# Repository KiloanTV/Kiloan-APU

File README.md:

<div>
  <h1 align="center">Kiloan APU V1</h1>

  <p align="center">
  <a href="https://hackclub.com/highway">
    </img>
  </a>
  </p>
  <h1></h1>
  <p align="center">
    The mainboard for a custom digital mixing console!
  </p>
</div>

<sub align="center">This work is licensed under the
[MIT License](https://mit-license.org).
</sub>

## Table of Contents

- [About](#about)
- [Pictures](#pictures)
- [Bill of Materials](#bill-of-materials)

# About

I've always wanted my own digital mixing console, but those things are just too expensive for teenagers. That's why I want to build my own! This is the mainboard, to which additional PCB boards will later be attached. They provide inputs/outputs (balanced XLR, of course), are responsible for the controls, and serve as a USB audio interface. This is the first step in this extensive project!

# Pictures

# Bill of Materials

|Reference                                        |Value                        |Description                                                                                                                 |Qty|LCSC           |Price|FIELD7                 |
|-------------------------------------------------|-----------------------------|----------------------------------------------------------------------------------------------------------------------------|---|---------------|-----|-----------------------|
|C1                                               |25V 10u0                     |                                                                                                                            |1  |C391262        |     |                       |
|C2,C5,C13,C20,C28,C30,C31,C32,C33,C35,C36,C37,C38|CAP_100n_50V_X7R_0805        |                                                                                                                            |13 |C3018562       |     |                       |
|C3,C4,C6,C18,C19,C21,C29,C34                     |CAP_10u0_25V_X5R_0805        |                                                                                                                            |8  |C391262        |     |                       |
|C7,C10                                           |25V 10uF                     |25V 10uF X5R ±20% 0805 Multilayer Ceramic Capacitors MLCC - SMD/SMT ROHS                                                    |2  |C391262        |     |                       |
|C8,C11                                           |50V 100nF                    |50V 100nF X7R ±10% 0805 Multilayer Ceramic Capacitors MLCC - SMD/SMT ROHS                                                   |2  |C3018562       |     |                       |
|C9                                               |50V 5.6nF                    |50V 5.6nF X7R ±10% 0805 Multilayer Ceramic Capacitors MLCC - SMD/SMT ROHS                                                   |1  |C113862        |     |                       |
|C12                                              |50V 150pF                    |50V 150pF C0G ±5% 0805 Multilayer Ceramic Capacitors MLCC - SMD/SMT ROHS                                                    |1  |C2168780       |     |                       |
|C14,C15                                          |50V 12pF                     |                                                                                                                            |2  |C2168859       |     |                       |
|C16,C17,C25,C26,C27                              |CAP_100u_20%_25V_ALUM_RADIAL |                                                                                                                            |5  |C108360,C136287|     |                       |
|C22,C23,C24                                      |330u_20%_25V_ALUM_RADIAL     |                                                                                                                            |3  |C47344178      |     |                       |
|FER1,FER2                                        |210mΩ 0805                   |210mΩ ±25% 600Ω@100MHz 0805 Ferrite Beads ROHS                                                                              |2  |C85837         |     |                       |
|IC1,IC5                                          |IC_LM1117MP-5.0              |                                                                                                                            |2  |C131933        |     |                       |
|IC2                                              |IC_NCP1117LPST33             |                                                                                                                            |1  |C146799        |     |                       |
|IC3                                              |IC_ADM811TARTZ               |                                                                                                                            |1  |C462205        |     |                       |
|IC4                                              |IC_TLE2426ID                 |                                                                                                                            |1  |C59459         |     |                       |
|IC6                                              |IC_25AA1024                  |                                                                                                                            |1  |C2653525       |     |                       |
|J1                                               |PowerConAD-Wandler           |Generic connector, single row, 01x04, script generated (kicad-library-utils/schlib/autogen/connector/)                      |1  |C131334        |     |                       |
|J2                                               |AD-Wandler CON               |Generic connector, single row, 01x08, script generated (kicad-library-utils/schlib/autogen/connector/)                      |1  |C157974        |     |                       |
|J3                                               |PowerConDA-Wandler           |Generic connector, single row, 01x04, script generated (kicad-library-utils/schlib/autogen/connector/)                      |1  |C131334        |     |                       |
|J4                                               |DA-Wandler CON               |Generic connector, single row, 01x08, script generated (kicad-library-utils/schlib/autogen/connector/)                      |1  |C157974        |     |                       |
|J5                                               |PowerCON ESP                 |Generic connector, single row, 01x02, script generated (kicad-library-utils/schlib/autogen/connector/)                      |1  |C131337        |     |                       |
|J6                                               |ESP CON                      |Generic connector, single row, 01x08, script generated (kicad-library-utils/schlib/autogen/connector/)                      |1  |C157974        |     |                       |
|J7                                               |PowerConXMOS                 |Generic connector, single row, 01x04, script generated (kicad-library-utils/schlib/autogen/connector/)                      |1  |C131334        |     |                       |
|J8                                               |XMOS CON                     |Generic connector, single row, 01x08, script generated (kicad-library-utils/schlib/autogen/connector/)                      |1  |C157974        |     |                       |
|J9                                               |AUXADC                       |Generic connector, single row, 01x05, script generated (kicad-library-utils/schlib/autogen/connector/)                      |1  |C157993        |     |                       |
|JP1                                              |CON_JUMPER                   |                                                                                                                            |1  |C492401        |     |                       |
|P1                                               |ADAU1452                     |Audio Processing Unit                                                                                                       |1  |C462188        |     |                       |
|Q1                                               |ST STD2805T4                 |PNP 60V 5A 150MHz 15W                                                                                                       |1  |C672201        |     |                       |
|R1,R2                                            |RES_2K00_1%_0.125W_Thick_0805|                                                                                                                            |2  |C114572        |     |                       |
|R3,R4,R7,R8                                      |33R0_5%_4x0603               |                                                                                                                            |4  |C872331        |     |                       |
|R5                                               |1kΩ 0805                     |125mW Thick Film Resistor 150V ±100ppm/℃ ±1% 1kΩ 0805 Chip Resistor - Surface Mount ROHS                                    |1  |C95781         |     |                       |
|R9                                               |RES_1K00_1%_0.125W_Thick_0805|                                                                                                                            |1  |C95781         |     |                       |
|R10                                              |4.32kΩ                       |125mW Thick Film Resistor 150V ±100ppm/℃ ±1% 4.32kΩ 0805 Chip Resistor - Surface Mount ROHS                                 |1  |C483139        |     |                       |
|R11                                              |RES_100K_1%_0.125W_Thick_0805|                                                                                                                            |1  |C96346         |     |                       |
|R12,R15,R16                                      |RES_10K0_1%_0.125W_Thick_0805|                                                                                                                            |3  |C84376         |     |                       |
|R13                                              |RES_33R0_1%_0.125W_Thick_0805|                                                                                                                            |1  |C126353        |     |                       |
|R14                                              |RES_100R_1%_0.125W_Thick_0805|                                                                                                                            |1  |C105577        |     |                       |
|X1                                               |PowerIN                      |2x2P 4P Micro-Fit(MX 3.0) Tin 3mm 2 -40℃~+105℃ 8.5A 2 3mm Brass Through Hole Through Hole,P=3mm Wire To Board Connector ROHS|1  |C277721        |     |                       |
|X2                                               |USBi                         |                                                                                                                            |1  |C18723067      |     |                       |
|X3                                               |ExpansionHeader              |                                                                                                                            |1  |C3324391       |     |                       |
|X4                                               |Power LED                    |Generic connector, single row, 01x03, script generated (kicad-library-utils/schlib/autogen/connector/)                      |1  |C122442        |     |                       |
|Y1                                               |24M576                       |                                                                                                                            |1  |C6040680       |     |                       |
|                                                 |                             |                                                                                                                            |   |               |     |Quote from LCSC: $27,07|
|                                                 |                             |                                                                                                                            |   |               |     |Quote from JLCPCB: 4.17 USD|
|                                                 |                             |                                                                                                                            |   |               |     |Quote Total: 31.24 USD|

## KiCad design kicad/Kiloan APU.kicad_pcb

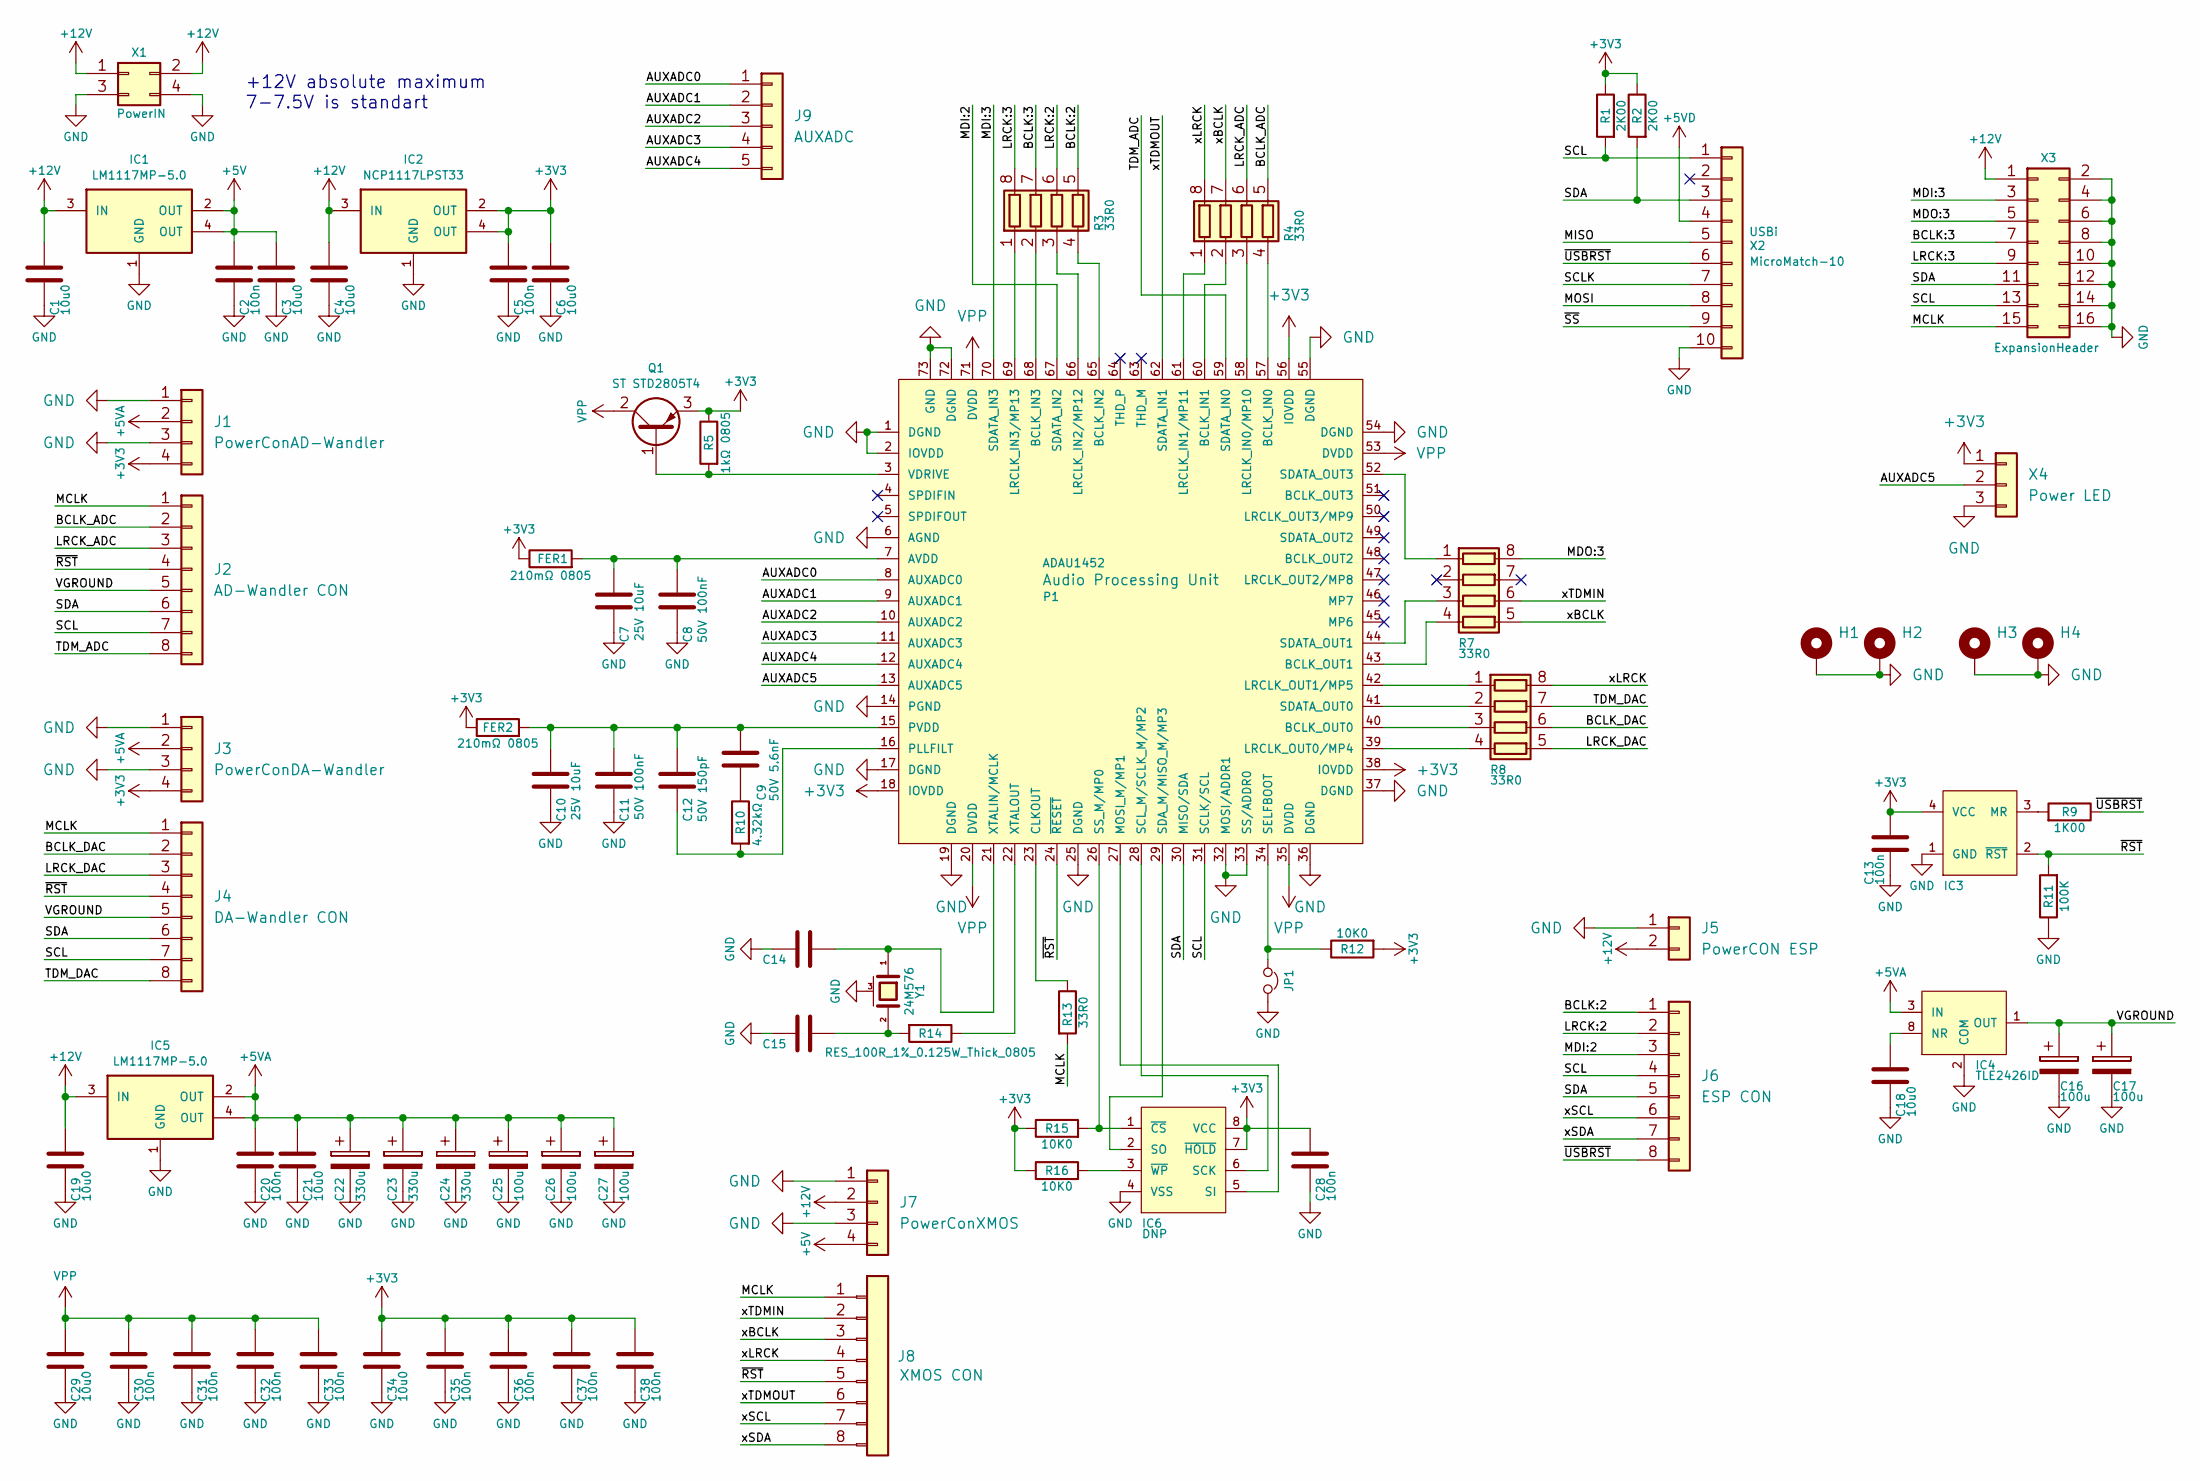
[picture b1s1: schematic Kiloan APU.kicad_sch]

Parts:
C1: 25V 10u0; C_0805_2012Metric; LCSC C391262
C2, C5, C13, C20, C28, C30, C31, C32, C33, C35, C36, C37, C38: CAP_100n_50V_X7R_0805; C_0805_2012Metric; LCSC C3018562
C3, C4, C6, C18, C19, C21, C29, C34: CAP_10u0_25V_X5R_0805; C_0805_2012Metric; LCSC C391262
C7, C10: 25V 10uF; C_0805_2012Metric; Part Number GRM21BR61E106MA73L; LCSC C391262
C8, C11: 50V 100nF; C_0805_2012Metric; Part Number C0805C104K5RACTU; LCSC C3018562
C9: 50V 5.6nF; C_0805_2012Metric; Part Number CC0805KRX7R9BB562; LCSC C113862
C12: 50V 150pF; C_0805_2012Metric; Part Number C0805C151J5GACTU; LCSC C2168780
C14, C15: 50V 12pF; C_0805_2012Metric; Part Number C0805C220J5GACTU; LCSC C2168859
C16, C17: CAP_100u_20%_25V_ALUM_RADIAL; CP_Radial_D5.0mm_P2.00mm; LCSC C136287
C22, C23, C24: 330u_20%_25V_ALUM_RADIAL; CP_Radial_D8.0mm_P3.50mm; LCSC C47344178
C25, C26, C27: CAP_100u_20%_25V_ALUM_RADIAL; CP_Radial_D5.0mm_P2.00mm; LCSC C108360
FER1, FER2: 210mΩ 0805; R_0805_2012Metric; Part Number BLM21AG601SN1D; LCSC C85837
H1, H2: MountingHole_Pad; MountingHole_2.2mm_M2_Pad_Via
H3, H4: MountingHole_Pad; MountingHole_3.2mm_M3_Pad_Via
IC1, IC5: IC_LM1117MP-5.0; SOT-223; LCSC C131933
IC2: IC_NCP1117LPST33; SOT-223; LCSC C146799
IC3: IC_ADM811TARTZ; SOT-143; Part Number ADM811TARTZ-REEL; LCSC C462205
IC4: IC_TLE2426ID; SOIC-8-1EP_3.9x4.9mm_P1.27mm_EP2.29x3mm; LCSC C59459
IC6: IC_25AA1024; SOIJ8-M_MC_MCH; LCSC C2653525
J1: PowerConAD-Wandler; JST_PH_B4B-PH-K_1x04_P2.00mm_Vertical; LCSC C131334
J2: AD-Wandler CON; JST_PH_B8B-PH-K_1x08_P2.00mm_Vertical; LCSC C157974
J3: PowerConDA-Wandler; JST_PH_B4B-PH-K_1x04_P2.00mm_Vertical; LCSC C131334
J4: DA-Wandler CON; JST_PH_B8B-PH-K_1x08_P2.00mm_Vertical; LCSC C157974
J5: PowerCON ESP; JST_PH_B2B-PH-K_1x02_P2.00mm_Vertical; LCSC C131337
J6: ESP CON; JST_PH_B8B-PH-K_1x08_P2.00mm_Vertical; LCSC C157974
J7: PowerConXMOS; JST_PH_B4B-PH-K_1x04_P2.00mm_Vertical; LCSC C131334
J8: XMOS CON; JST_PH_B8B-PH-K_1x08_P2.00mm_Vertical; LCSC C157974
J9: AUXADC; JST_PH_B5B-PH-K_1x05_P2.00mm_Vertical; LCSC C157993
JP1: CON_JUMPER; PinHeader_1x02_P2.54mm_Vertical; LCSC C492401
P1: ADAU1452; CP-72-6_ADI-M; Part Number ADAU1452WBCPZ-RL; LCSC C462188
Q1: ST STD2805T4; TO-252-2; Part Number STD2805T4; LCSC C672201
R1, R2: RES_2K00_1%_0.125W_Thick_0805; R_0805_2012Metric; LCSC C114572
R3, R4, R7, R8: 33R0_5%_4x0603; R_Array_Convex_4x0603; LCSC C872331
R5: 1kΩ 0805; R_0805_2012Metric; Part Number RC0805FR-071KL; LCSC C95781
R9: RES_1K00_1%_0.125W_Thick_0805; R_0805_2012Metric; LCSC C95781
R10: 4.32kΩ; R_0805_2012Metric; Part Number RC0805FR-074K32L; LCSC C483139
R11: RES_100K_1%_0.125W_Thick_0805; R_0805_2012Metric; LCSC C96346
R12, R15, R16: RES_10K0_1%_0.125W_Thick_0805; R_0805_2012Metric; LCSC C84376
R13: RES_33R0_1%_0.125W_Thick_0805; R_0805_2012Metric; LCSC C126353
R14: RES_100R_1%_0.125W_Thick_0805; R_0805_2012Metric; LCSC C105577
X1: PowerIN; Molex_Micro-Fit_3.0_43045-0412_2x02_P3.00mm_Vertical; Part Number 430450412; LCSC C277721
X2: USBi; PinHeader_2x05_P2.00mm_Vertical; LCSC C18723067
X3: ExpansionHeader; JST_PHD_B16B-PHDSS_2x08_P2.00mm_Vertical; LCSC C3324391
X4: Power LED; Molex_PicoBlade_53047-0310_1x03_P1.25mm_Vertical; LCSC C122442
Y1: 24M576; Crystal_SMD_3225-4Pin_3.2x2.5mm; LCSC C6040680

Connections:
+3V3: C5.1, C6.1, C13.1, C28.1, C34.1, C35.1, C36.1, C37.1, C38.1, FER1.1, FER2.1, IC2.2 (OUT), IC2.4 (OUT), IC3.4 (VCC), IC6.7 (~HOLD), IC6.8 (VCC), J1.4 (3V3), J3.4 (3V3), P1.18 (IOVDD), P1.38 (IOVDD), P1.56 (IOVDD), Q1.3 (E), R1.1, R2.1, R5.1, R12.2, R15.1, R16.1, X4.1
+5V: C2.1, C3.1, IC1.2 (OUT), IC1.4 (OUT), J7.4 (5V)
+5VA: C20.1, C21.1, C22.1, C23.1, C24.1, C25.1, C26.1, C27.1, IC4.3 (IN), IC5.2 (OUT), IC5.4 (OUT), J1.2 (5VA), J3.2 (5VA)
+5VD: X2.4
+12V: C1.1, C4.1, C19.1, IC1.3 (IN), IC2.3 (IN), IC5.3 (IN), J5.2 (12V), J7.2 (12V), X1.1, X1.2, X3.1
/AUXADC0: J9.1, P1.8 (AUXADC0)
/AUXADC1: J9.2, P1.9 (AUXADC1)
/AUXADC2: J9.3, P1.10 (AUXADC2)
/AUXADC3: J9.4, P1.11 (AUXADC3)
/AUXADC4: J9.5, P1.12 (AUXADC4)
/AUXADC5: P1.13 (AUXADC5), X4.2
/BCLK:2: J6.1 (BCLK), R3.5 (R4.2)
/BCLK:3: R3.7 (R2.2), X3.7
/BCLK_ADC: J2.2 (BCLK), R4.5 (R4.2)
/BCLK_DAC: J4.2 (BCLK), R8.6 (R3.2)
/LRCK:2: J6.2 (LRCK), R3.6 (R3.2)
/LRCK:3: R3.8 (R1.2), X3.9
/LRCK_ADC: J2.3 (LRCK), R4.6 (R3.2)
/LRCK_DAC: J4.3 (LRCK), R8.5 (R4.2)
/MCLK: J2.1 (MCLK), J4.1 (MCLK), J8.1 (MCLK), R13.2, X3.15
/MDI:2: J6.3 (SDATA), P1.67 (SDATA_IN2)
/MDI:3: P1.70 (SDATA_IN3), X3.3
/MDO:3: R7.8 (R1.2), X3.5
/MISO: X2.5
/MOSI: X2.8
/SCL: J2.7 (SCL), J4.7 (SCL), J6.4 (SCL1), P1.31 (SCLK/SCL), R1.2, X2.1, X3.13
/SCLK: X2.7
/SDA: J2.6 (SDA), J4.6 (SDA), J6.5 (SDA1), P1.30 (MISO/SDA), R2.2, X2.3, X3.11
/TDM_ADC: J2.8 (TDM), P1.59 (SDATA_IN0)
/TDM_DAC: J4.8 (TDM), R8.7 (R2.2)
/VGROUND: C16.1, C17.1, IC4.1 (OUT), J2.5 (VGROUND), J4.5 (VGROUND)
/xBCLK: J8.3 (XBCLK), R4.7 (R2.2), R7.5 (R4.2)
/xLRCK: J8.4 (XLRCK), R4.8 (R1.2), R8.8 (R1.2)
/xSCL: J6.6 (SCL2), J8.7 (SCL)
/xSDA: J6.7 (SDA2), J8.8 (SDA)
/xTDMIN: J8.2 (XTDMIN1), R7.6 (R3.2)
/xTDMOUT: J8.6 (XTDMOUT1), P1.62 (SDATA_IN1)
/~RST: IC3.2 (~RST), J2.4 (RST), J4.4 (RST), J8.5 (RST), P1.24 (~RESET), R11.2
/~SS: X2.9
/~USBRST: J6.8 (MRST), R9.1, X2.6
GND: C1.2, C2.2, C3.2, C4.2, C5.2, C6.2, C7.2, C8.2, C10.2, C11.2, C13.2, C14.2, C15.2, C16.2, C17.2, C18.2, C19.2, C20.2, C21.2, C22.2, C23.2, C24.2, C25.2, C26.2, C27.2, C28.2, C29.2, C30.2, C31.2, C32.2, C33.2, C34.2, C35.2, C36.2, C37.2, C38.2, H1.1, H2.1, H3.1, H4.1, IC1.1 (GND), IC2.1 (GND), IC3.1 (GND), IC4.2 (COM), IC5.1 (GND), IC6.4 (VSS), J1.1 (GND), J1.3 (GND), J3.1 (GND), J3.3 (GND), J5.1 (GND), J7.1 (GND), J7.3 (GND), JP1.2, P1.1 (DGND), P1.2 (IOVDD), P1.6 (AGND), P1.14 (PGND), P1.17 (DGND), P1.19 (DGND), P1.25 (DGND), P1.32 (MOSI/ADDR1), P1.33 (SS/ADDR0), P1.36 (DGND), P1.37 (DGND), P1.54 (DGND), P1.55 (DGND), P1.72 (DGND), P1.73 (GND), R11.1, X1.3, X1.4, X2.10, X3.2, X3.4, X3.6, X3.8, X3.10, X3.12, X3.14, X3.16, X4.3, Y1.3 (case)
unnamed: C9.2, R10.1
unnamed: C15.1, R14.2, Y1.2
unnamed: IC3.3 (MR), R9.2
unnamed: C18.1, IC4.8 (NR)
unnamed: IC6.6 (SCK), P1.28 (SCL_M/SCLK_M/MP2)
unnamed: IC6.5 (SI), P1.27 (MOSI_M/MP1)
unnamed: IC6.2 (SO), P1.29 (SDA_M/MISO_M/MP3)
unnamed: IC6.1 (~CS), P1.26 (SS_M/MP0), R15.2
unnamed: IC6.3 (~WP), R16.2
unnamed: C7.1, C8.1, FER1.2, P1.7 (AVDD)
unnamed: P1.57 (BCLK_IN0), R4.4 (R4.1)
unnamed: P1.60 (BCLK_IN1), R4.2 (R2.1)
unnamed: P1.65 (BCLK_IN2), R3.4 (R4.1)
unnamed: P1.68 (BCLK_IN3), R3.2 (R2.1)
unnamed: P1.40 (BCLK_OUT0), R8.3 (R3.1)
unnamed: P1.43 (BCLK_OUT1), R7.4 (R4.1)
unnamed: P1.23 (CLKOUT), R13.1
unnamed: P1.58 (LRCLK_IN0/MP10), R4.3 (R3.1)
unnamed: P1.61 (LRCLK_IN1/MP11), R4.1 (R1.1)
unnamed: P1.66 (LRCLK_IN2/MP12), R3.3 (R3.1)
unnamed: P1.69 (LRCLK_IN3/MP13), R3.1 (R1.1)
unnamed: P1.39 (LRCLK_OUT0/MP4), R8.4 (R4.1)
unnamed: P1.42 (LRCLK_OUT1/MP5), R8.1 (R1.1)
unnamed: C12.2, P1.16 (PLLFILT), R10.2
unnamed: C9.1, C10.1, C11.1, C12.1, FER2.2, P1.15 (PVDD)
unnamed: P1.41 (SDATA_OUT0), R8.2 (R2.1)
unnamed: P1.44 (SDATA_OUT1), R7.3 (R3.1)
unnamed: P1.52 (SDATA_OUT3), R7.1 (R1.1)
unnamed: JP1.1, P1.34 (SELFBOOT), R12.1
unnamed: P1.3 (VDRIVE), Q1.1 (B), R5.2
unnamed: C14.1, P1.21 (XTALIN/MCLK), Y1.1
unnamed: P1.22 (XTALOUT), R14.1
VPP: C29.1, C30.1, C31.1, C32.1, C33.1, P1.20 (DVDD), P1.35 (DVDD), P1.53 (DVDD), P1.71 (DVDD), Q1.2 (C)

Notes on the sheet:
+12V absolute maximum 7-7.5V is standart

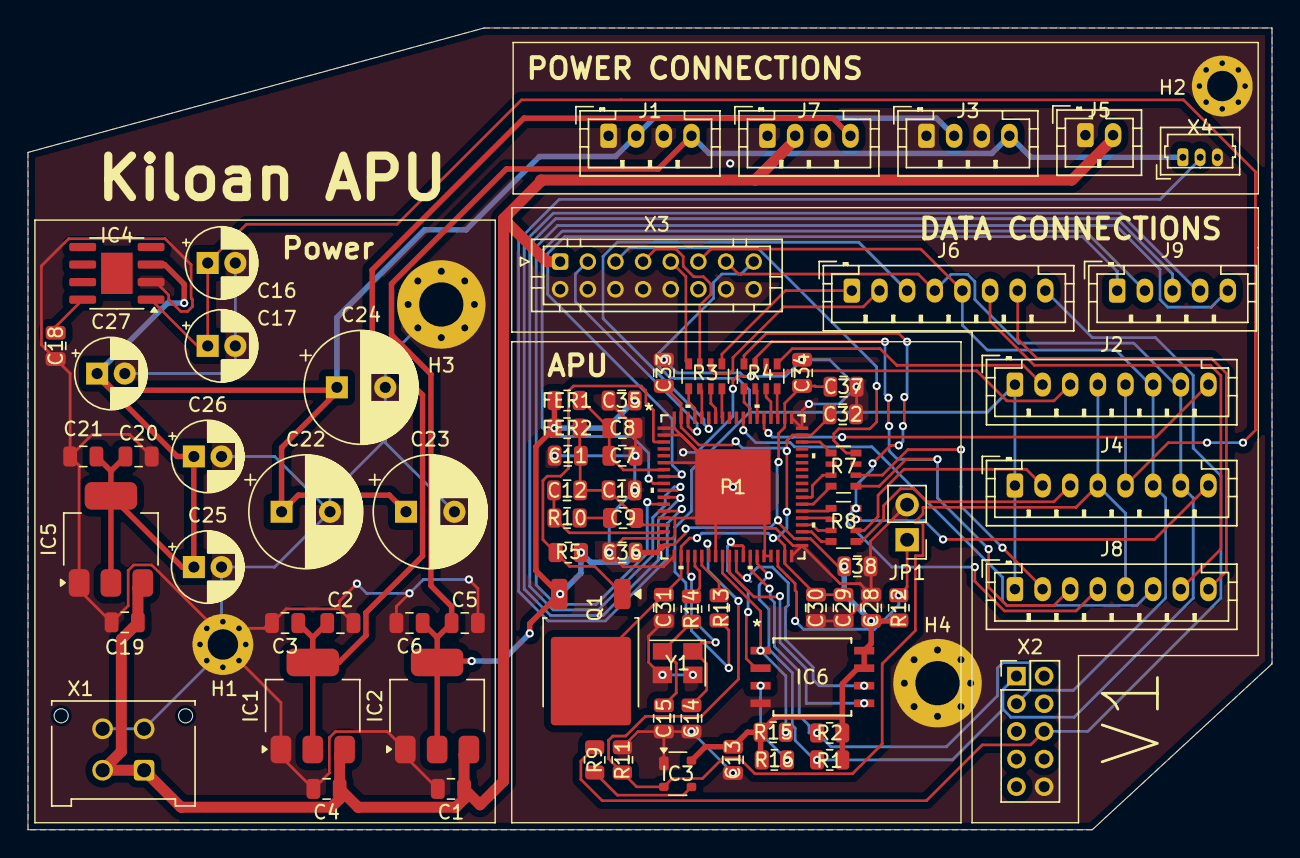
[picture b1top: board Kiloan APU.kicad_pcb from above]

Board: 2 copper layers, 90.0 x 58.0 mm, 82 parts (0 on the bottom side), 69 nets.

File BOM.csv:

"Reference","Value","Description","Qty","LCSC","Price"
"C1","25V 10u0","","1","C391262",""
"C2,C5,C13,C20,C28,C30,C31,C32,C33,C35,C36,C37,C38","CAP_100n_50V_X7R_0805","","13","C3018562",""
"C3,C4,C6,C18,C19,C21,C29,C34","CAP_10u0_25V_X5R_0805","","8","C391262",""
"C7,C10","25V 10uF","25V 10uF X5R ±20% 0805 Multilayer Ceramic Capacitors MLCC - SMD/SMT ROHS","2","C391262",""
"C8,C11","50V 100nF","50V 100nF X7R ±10% 0805 Multilayer Ceramic Capacitors MLCC - SMD/SMT ROHS","2","C3018562",""
"C9","50V 5.6nF","50V 5.6nF X7R ±10% 0805 Multilayer Ceramic Capacitors MLCC - SMD/SMT ROHS","1","C113862",""
"C12","50V 150pF","50V 150pF C0G ±5% 0805 Multilayer Ceramic Capacitors MLCC - SMD/SMT ROHS","1","C2168780",""
"C14,C15","50V 12pF","","2","C2168859",""
"C16,C17,C25,C26,C27","CAP_100u_20%_25V_ALUM_RADIAL","","5","C108360,C136287",""
"C22,C23,C24","330u_20%_25V_ALUM_RADIAL","","3","C47344178",""
"FER1,FER2","210mΩ 0805","210mΩ ±25% 600Ω@100MHz 0805 Ferrite Beads ROHS","2","C85837",""
"IC1,IC5","IC_LM1117MP-5.0","","2","C131933",""
"IC2","IC_NCP1117LPST33","","1","C146799",""
"IC3","IC_ADM811TARTZ","","1","C462205",""
"IC4","IC_TLE2426ID","","1","C59459",""
"IC6","IC_25AA1024","","1","C2653525",""
"J1","PowerConAD-Wandler","Generic connector, single row, 01x04, script generated (kicad-library-utils/schlib/autogen/connector/)","1","C131334",""
"J2","AD-Wandler CON","Generic connector, single row, 01x08, script generated (kicad-library-utils/schlib/autogen/connector/)","1","C157974",""
"J3","PowerConDA-Wandler","Generic connector, single row, 01x04, script generated (kicad-library-utils/schlib/autogen/connector/)","1","C131334",""
"J4","DA-Wandler CON","Generic connector, single row, 01x08, script generated (kicad-library-utils/schlib/autogen/connector/)","1","C157974",""
"J5","PowerCON ESP","Generic connector, single row, 01x02, script generated (kicad-library-utils/schlib/autogen/connector/)","1","C131337",""
"J6","ESP CON","Generic connector, single row, 01x08, script generated (kicad-library-utils/schlib/autogen/connector/)","1","C157974",""
"J7","PowerConXMOS","Generic connector, single row, 01x04, script generated (kicad-library-utils/schlib/autogen/connector/)","1","C131334",""
"J8","XMOS CON","Generic connector, single row, 01x08, script generated (kicad-library-utils/schlib/autogen/connector/)","1","C157974",""
"J9","AUXADC","Generic connector, single row, 01x05, script generated (kicad-library-utils/schlib/autogen/connector/)","1","C157993",""
"JP1","CON_JUMPER","","1","C492401",""
"P1","ADAU1452","Audio Processing Unit","1","C462188",""
"Q1","ST STD2805T4","PNP 60V 5A 150MHz 15W","1","C672201",""
"R1,R2","RES_2K00_1%_0.125W_Thick_0805","","2","C114572",""
"R3,R4,R7,R8","33R0_5%_4x0603","","4","C872331",""
"R5","1kΩ 0805","125mW Thick Film Resistor 150V ±100ppm/℃ ±1% 1kΩ 0805 Chip Resistor - Surface Mount ROHS","1","C95781",""
"R9","RES_1K00_1%_0.125W_Thick_0805","","1","C95781",""
"R10","4.32kΩ","125mW Thick Film Resistor 150V ±100ppm/℃ ±1% 4.32kΩ 0805 Chip Resistor - Surface Mount ROHS","1","C483139",""
"R11","RES_100K_1%_0.125W_Thick_0805","","1","C96346",""
"R12,R15,R16","RES_10K0_1%_0.125W_Thick_0805","","3","C84376",""
"R13","RES_33R0_1%_0.125W_Thick_0805","","1","C126353",""
"R14","RES_100R_1%_0.125W_Thick_0805","","1","C105577",""
"X1","PowerIN","2x2P 4P Micro-Fit(MX 3.0) Tin 3mm 2 -40℃~+105℃ 8.5A 2 3mm Brass Through Hole Through Hole,P=3mm Wire To Board Connector ROHS","1","C277721",""
"X2","USBi","","1","C18723067",""
"X3","ExpansionHeader","","1","C3324391",""
"X4","Power LED","Generic connector, single row, 01x03, script generated (kicad-library-utils/schlib/autogen/connector/)","1","C122442",""
"Y1","24M576","","1","C6040680",""
,"","","","","","Quote from LCSC: $27,07"
,"","","","","","Quote from JLCPCB: 4.17 USD"
,"","","","","","Total: 31.24 USD"

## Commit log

2025-07-31 add log and files from 30&31
2025-08-01 some more details
